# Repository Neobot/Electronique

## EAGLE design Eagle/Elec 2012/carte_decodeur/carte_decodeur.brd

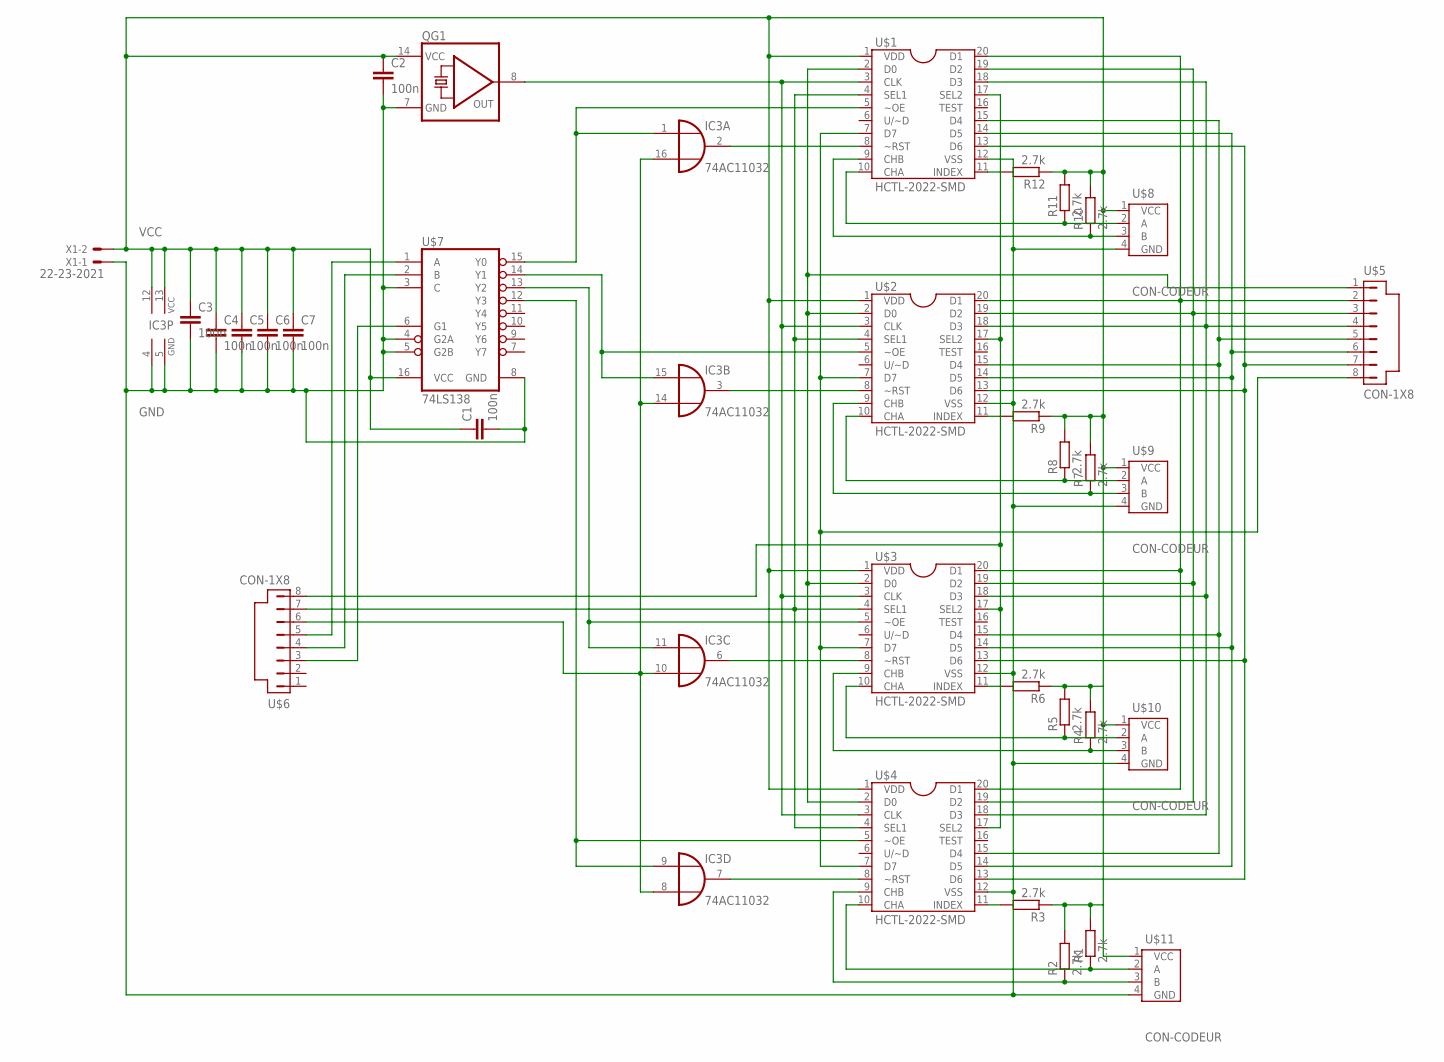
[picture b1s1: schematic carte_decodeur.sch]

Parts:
C1, C2, C3, C4, C5, C6, C7: 100n; C0805
IC3: 74AC11032; DIL16
QG1: QG5860; DIL14S
R1, R2, R3, R4, R5, R6, R7, R8, R9, R10, R11, R12: 2.7k; R0805
U$1, U$2, U$3, U$4: HCTL-2022-SMD; DIL20-SMD
U$5, U$6: CON-1X8
U$7: 74LS138; DIL16
U$8, U$9, U$10, U$11: CON-CODEUR; CON-1X4
X1: 22-23-2021

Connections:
GND: C1.2, C2.2, C3.2, C4.2, C5.2, C6.2, C7.2, IC3.4 (GND), IC3.5 (GND), QG1.7 (GND), U$1.12 (VSS), U$2.12 (VSS), U$3.12 (VSS), U$4.12 (VSS), U$7.3 (C), U$7.4 (G2A), U$7.5 (G2B), U$7.8 (GND), U$8.4 (GND), U$9.4 (GND), U$10.4 (GND), U$11.4 (GND), X1.1
unnamed: U$1.15 (D4), U$2.15 (D4), U$3.15 (D4), U$4.15 (D4), U$5.5
unnamed: U$1.19 (D2), U$2.19 (D2), U$3.19 (D2), U$4.19 (D2), U$5.3
unnamed: U$1.18 (D3), U$2.18 (D3), U$3.18 (D3), U$4.18 (D3), U$5.4
unnamed: IC3.1 (I1), U$1.5 (~OE), U$7.15 (Y0)
unnamed: IC3.15 (I1), U$2.5 (~OE), U$7.14 (Y1)
unnamed: U$1.13 (D6), U$2.13 (D6), U$3.13 (D6), U$4.13 (D6), U$5.7
unnamed: U$1.7 (D7), U$2.7 (D7), U$3.7 (D7), U$4.7 (D7), U$5.8
unnamed: U$1.2 (D0), U$2.2 (D0), U$3.2 (D0), U$4.2 (D0), U$5.1
unnamed: U$1.20 (D1), U$2.20 (D1), U$3.20 (D1), U$4.20 (D1), U$5.2
unnamed: IC3.11 (I1), U$3.5 (~OE), U$7.13 (Y2)
unnamed: IC3.9 (I1), U$4.5 (~OE), U$7.12 (Y3)
unnamed: U$1.4 (SEL1), U$2.4 (SEL1), U$3.4 (SEL1), U$4.4 (SEL1), U$6.7
unnamed: U$1.17 (SEL2), U$2.17 (SEL2), U$3.17 (SEL2), U$4.17 (SEL2), U$6.8
unnamed: U$1.14 (D5), U$2.14 (D5), U$3.14 (D5), U$4.14 (D5), U$5.6
unnamed: U$6.5, U$7.1 (A)
unnamed: U$6.4, U$7.2 (B)
unnamed: IC3.7 (O), U$4.8 (~RST)
unnamed: IC3.6 (O), U$3.8 (~RST)
unnamed: IC3.3 (O), U$2.8 (~RST)
unnamed: IC3.2 (O), U$1.8 (~RST)
unnamed: U$6.3, U$7.6 (G1)
unnamed: IC3.8 (I2), IC3.10 (I2), IC3.14 (I2), U$6.6
unnamed: R1.1, U$4.10 (CHA), U$11.2 (A)
unnamed: R2.1, U$4.9 (CHB), U$11.3 (B)
unnamed: QG1.8 (OUT), U$1.3 (CLK), U$2.3 (CLK), U$3.3 (CLK), U$4.3 (CLK)
unnamed: R3.2, U$4.11 (INDEX)
unnamed: R5.1, U$3.10 (CHA), U$10.2 (A)
unnamed: R4.1, U$3.9 (CHB), U$10.3 (B)
unnamed: R6.2, U$3.11 (INDEX)
unnamed: R9.2, U$2.11 (INDEX)
unnamed: R8.1, U$2.10 (CHA), U$9.2 (A)
unnamed: R7.1, U$2.9 (CHB), U$9.3 (B)
unnamed: R12.2, U$1.11 (INDEX)
unnamed: R11.1, U$1.10 (CHA), U$8.2 (A)
unnamed: R10.1, U$1.9 (CHB), U$8.3 (B)
VCC: C1.1, C2.1, C3.1, C4.1, C5.1, C6.1, C7.1, IC3.12 (VCC), IC3.13 (VCC), QG1.14 (VCC), R1.2, R2.2, R3.1, R4.2, R5.2, R6.1, R7.2, R8.2, R9.1, R10.2, R11.2, R12.1, U$1.1 (VDD), U$2.1 (VDD), U$3.1 (VDD), U$4.1 (VDD), U$7.16 (VCC), U$8.1 (VCC), U$9.1 (VCC), U$10.1 (VCC), U$11.1 (VCC), X1.2

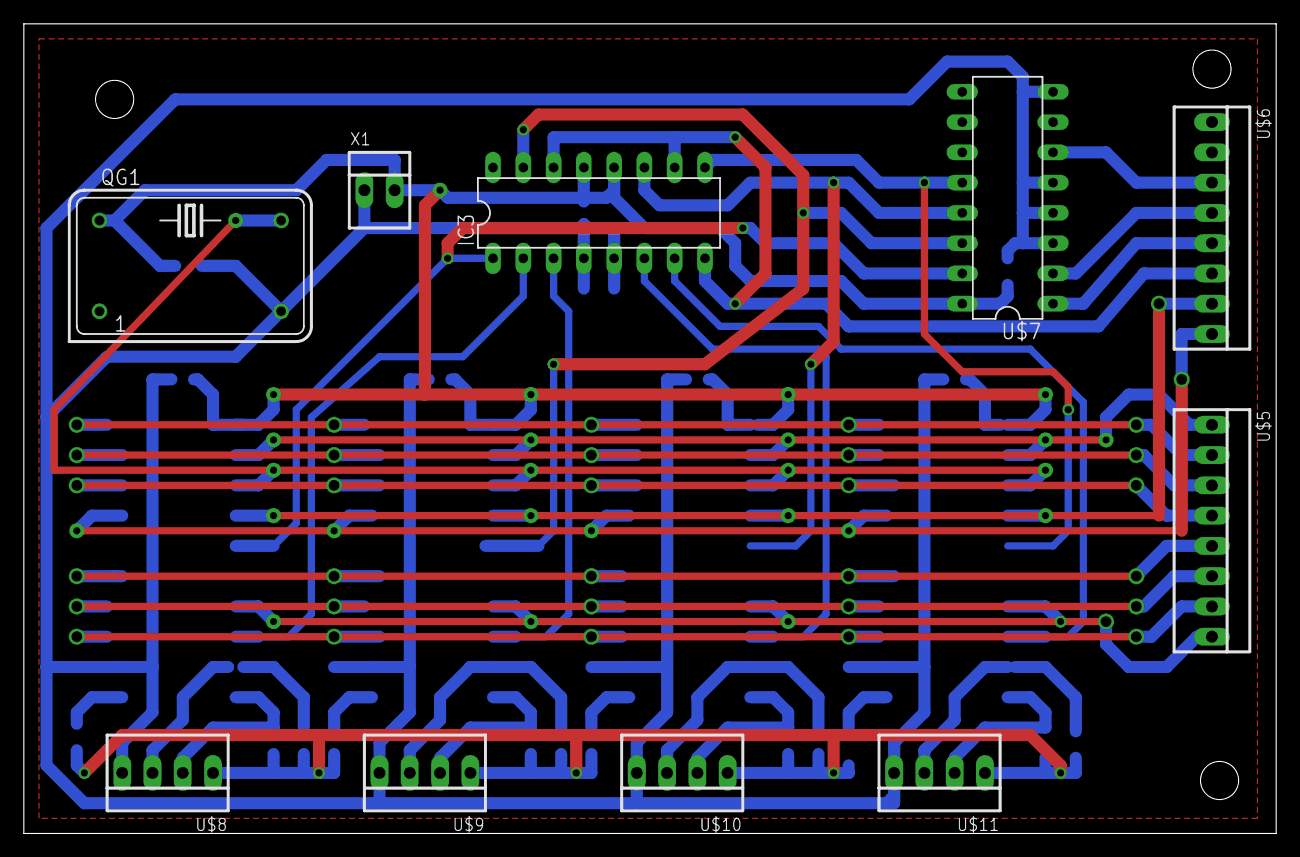
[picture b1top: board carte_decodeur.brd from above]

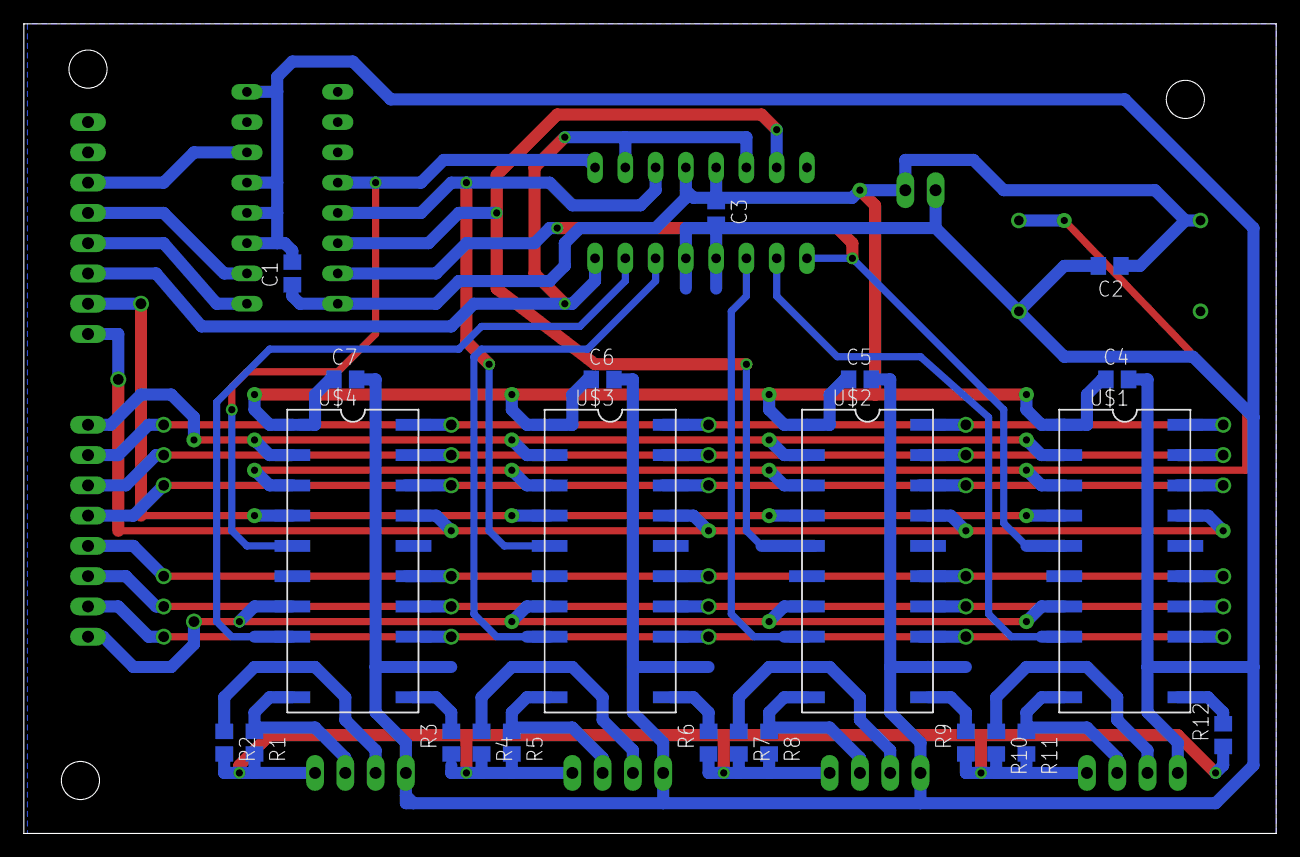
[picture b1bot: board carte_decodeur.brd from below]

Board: 2 copper layers, 105.1 x 67.9 mm, 33 parts (23 on the bottom side), 37 nets.

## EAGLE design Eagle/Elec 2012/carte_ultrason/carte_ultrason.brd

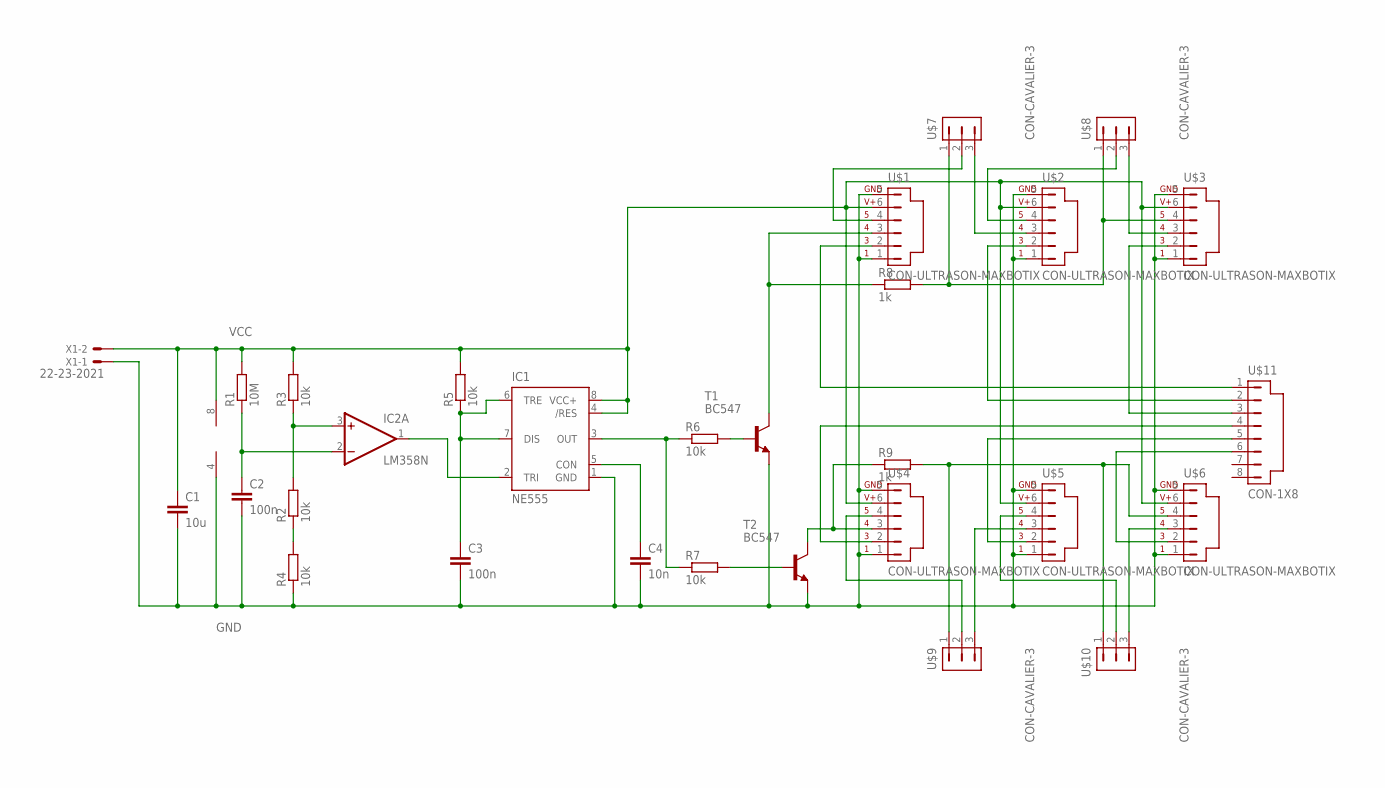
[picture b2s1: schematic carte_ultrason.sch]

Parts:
C1: 10u; C1206K
C2, C3: 100n; C0805K
C4: 10n; C0805K
IC1: NE555; DIL-08
IC2: LM358N; DIL08
R1: 10M; R0805W
R2, R4, R5: 10k; R0805W
R3, R6, R7: 10k; 0207/10
R8: 1k; 0207/10
R9: 1k; R0805W
T1, T2: BC547; TO92
U$1, U$2, U$3, U$4, U$5, U$6: CON-ULTRASON-MAXBOTIX; CON-1X6
U$7, U$8, U$9, U$10: CON-CAVALIER-3
U$11: CON-1X8
X1: 22-23-2021

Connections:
GND: C1.2, C2.2, C3.2, C4.2, IC1.1 (GND), IC2.4 (V-), R4.1, T1.1 (E), T2.1 (E), U$1.1, U$1.5 (GND), U$2.1, U$2.5 (GND), U$3.1, U$3.5 (GND), U$4.1, U$4.5 (GND), U$5.1, U$5.5 (GND), U$6.1, U$6.5 (GND), X1.1
unnamed: IC1.2 (TRI), IC2.1 (OUT)
unnamed: C3.1, IC1.6 (TRE), IC1.7 (DIS), R5.1
unnamed: C2.1, IC2.2 (-IN), R1.1
unnamed: R2.1, R4.2
unnamed: IC2.3 (+IN), R2.2, R3.1
unnamed: C4.1, IC1.5 (CON)
unnamed: IC1.3 (OUT), R6.1, R7.1
unnamed: R6.2, T1.2 (B)
unnamed: R7.2, T2.2 (B)
unnamed: U$1.4, U$7.2
unnamed: R9.1, T2.3 (C), U$4.3
unnamed: U$6.2, U$11.6
unnamed: U$2.3, U$7.3
unnamed: U$2.4, U$8.2
unnamed: U$3.3, U$8.3
unnamed: U$4.4, U$9.2
unnamed: R9.2, U$6.4, U$9.1, U$10.1
unnamed: U$5.3, U$9.3
unnamed: U$5.4, U$10.2
unnamed: U$6.3, U$10.3
unnamed: U$5.2, U$11.5
unnamed: R8.2, U$3.4, U$7.1, U$8.1
unnamed: U$4.2, U$11.4
unnamed: U$1.2, U$11.1
unnamed: U$3.2, U$11.3
unnamed: U$2.2, U$11.2
unnamed: R8.1, T1.3 (C), U$1.3
VCC: C1.1, IC1.4 (/RES), IC1.8 (VCC+), IC2.8 (V+), R1.2, R3.2, R5.2, U$1.6 (V+), U$2.6 (V+), U$3.6 (V+), U$4.6 (V+), U$5.6 (V+), U$6.6 (V+), X1.2

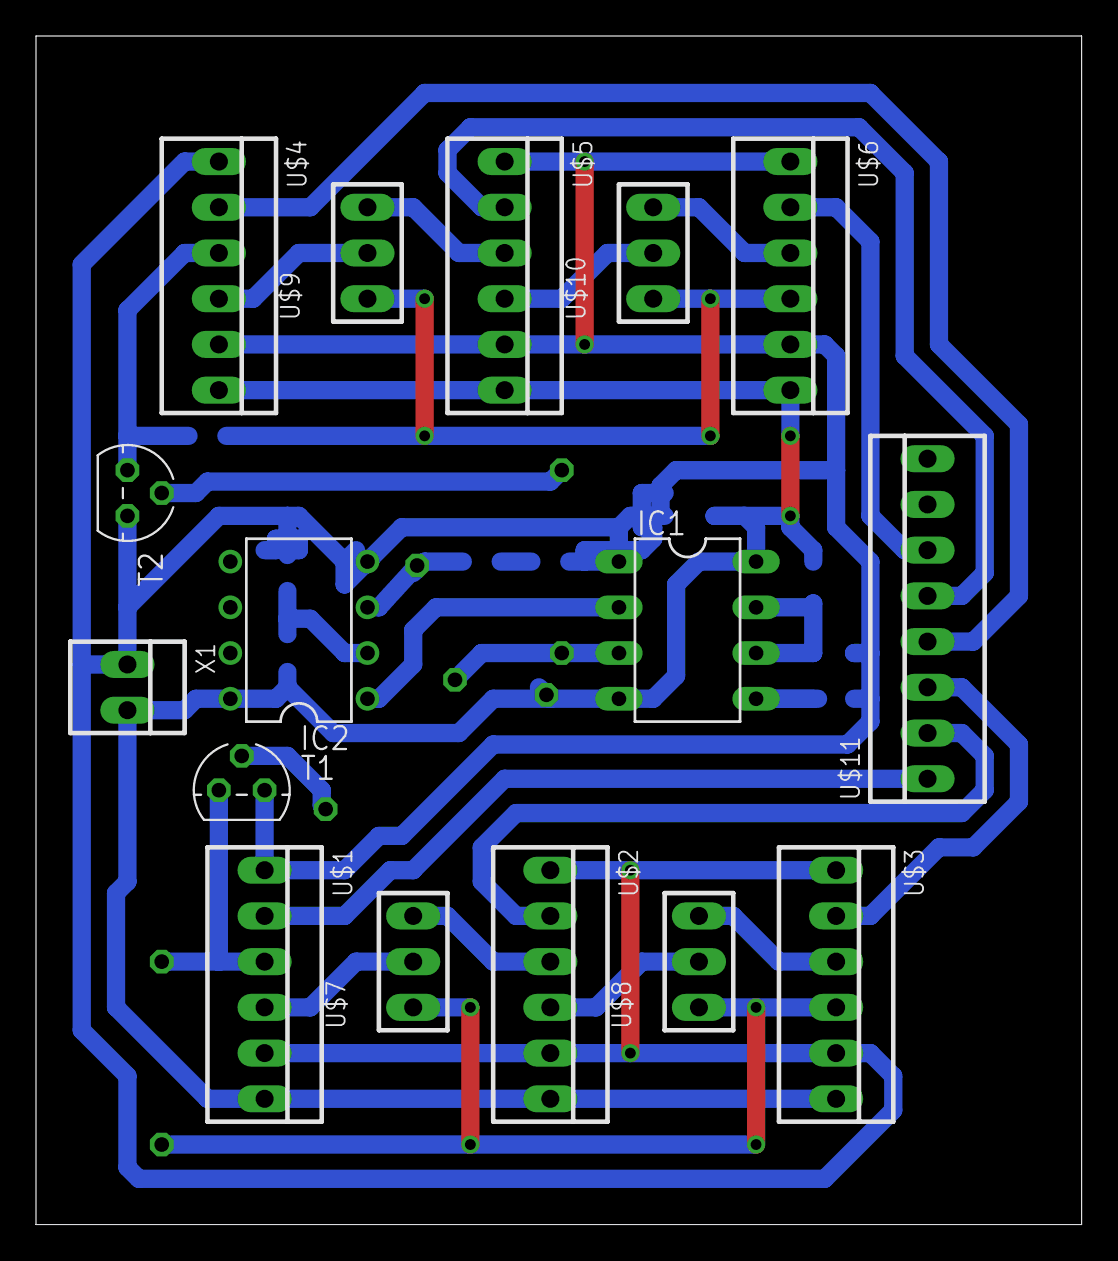
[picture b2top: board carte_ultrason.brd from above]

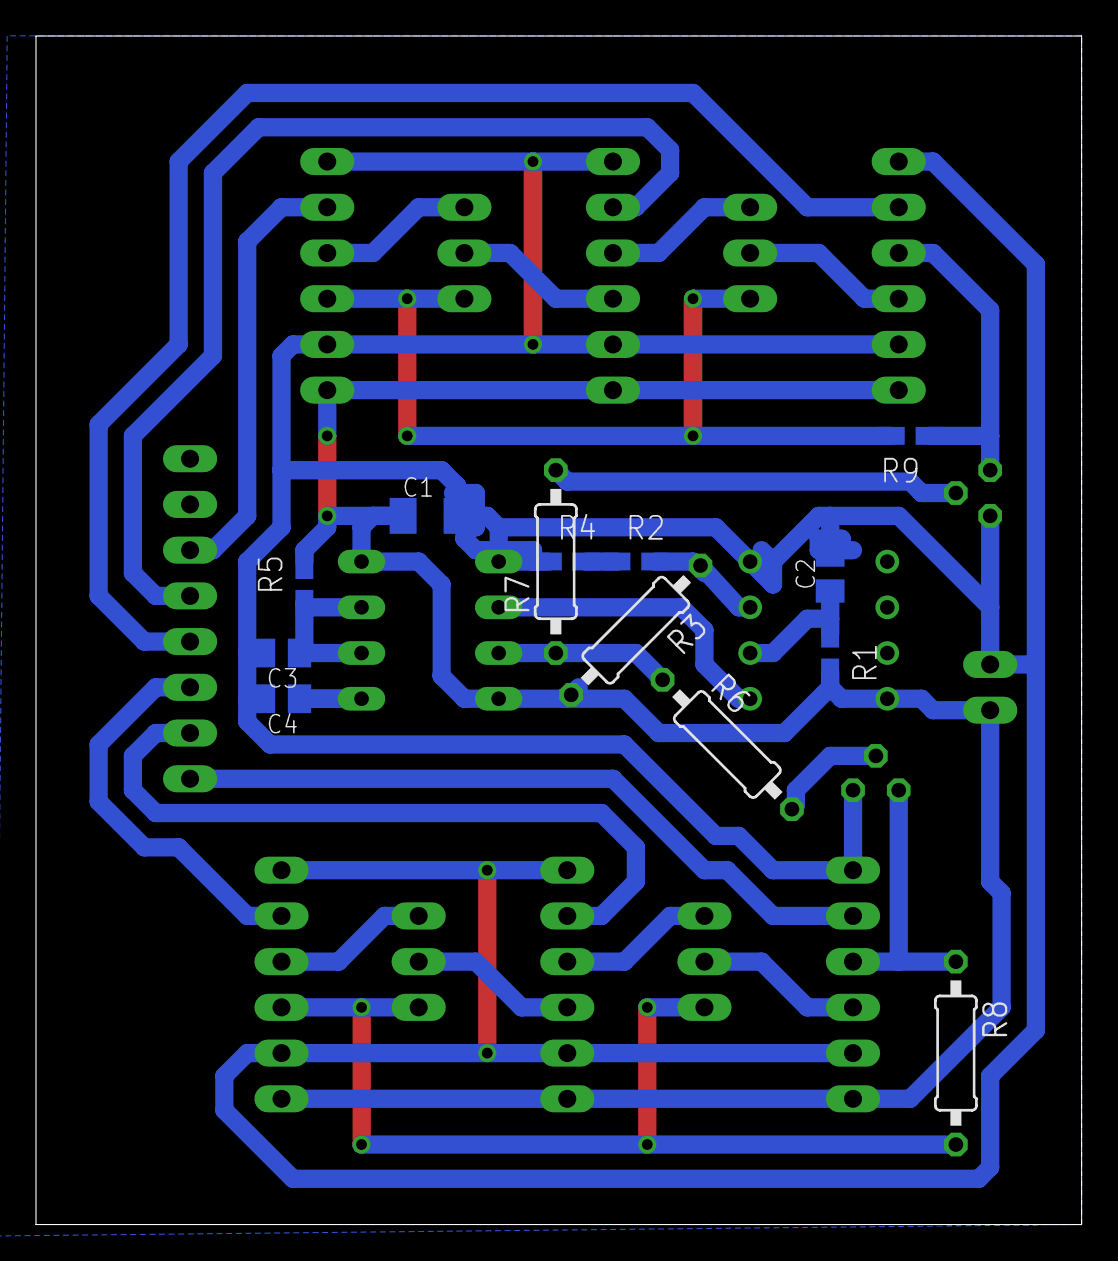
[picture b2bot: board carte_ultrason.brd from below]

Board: 2 copper layers, 58.1 x 66.0 mm, 29 parts (13 on the bottom side), 29 nets.

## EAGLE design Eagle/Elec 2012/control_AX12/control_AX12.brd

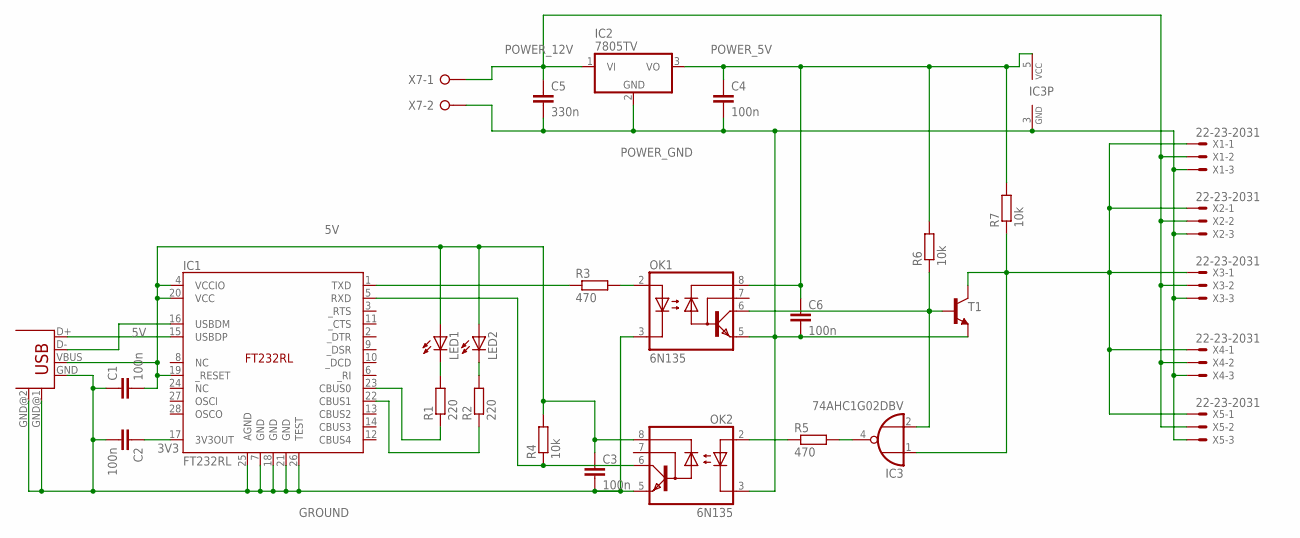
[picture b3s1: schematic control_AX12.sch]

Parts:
C1, C2, C3, C4, C6: 100n; C0805
C5: 330n; C0805
IC1: FT232RL; SSOP-28
IC2: 7805TV; TO220V
IC3: 74AHC1G02DBV; SOT23-5
LED1, LED2: LED5MM
OK1, OK2: 6N135; DIL08
R1, R2: 220; M0805
R3, R5: 470; 0207/10
R4, R6, R7: 10k; 0207/10
T1: BC547-NPN-TO92-CBE; TO92-CBE
USB1: USB-B-H
X1, X2, X3, X4, X5: 22-23-2031
X7: W237-02P; W237-132

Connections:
3V3: C2.1, IC1.17 (3V3OUT)
5V: C1.2, C3.1, IC1.4 (VCCIO), IC1.19 (_RESET), IC1.20 (VCC), LED1.A, LED2.A, OK2.8 (VCC), R4.2, USB1.VBUS
GROUND: C1.1, C2.2, C3.2, IC1.7 (GND), IC1.18 (GND), IC1.21 (GND), IC1.25 (AGND), IC1.26 (TEST), OK1.3 (C), OK2.5 (GND), USB1.GND, USB1.GND@1 (GND), USB1.GND@2 (GND)
unnamed: IC1.22 (CBUS1), R2.1
unnamed: IC1.1 (TXD), R3.1
unnamed: IC1.5 (RXD), OK2.6 (VO), R4.1
unnamed: IC1.23 (CBUS0), R1.1
unnamed: LED1.K (C), R1.2
unnamed: LED2.K (C), R2.2
unnamed: OK1.2 (A), R3.2
unnamed: IC1.16 (USBDM), USB1.D-
unnamed: IC1.15 (USBDP), USB1.D+
unnamed: OK2.2 (A), R5.1
unnamed: IC3.4 (O), R5.2
unnamed: IC3.2 (I1), OK1.6 (VO), R6.1, T1.B
unnamed: IC3.1 (I0), R7.1, T1.C, X1.1, X2.1, X3.1, X4.1, X5.1
POWER_5V: C4.1, C6.1, IC2.3 (VO), IC3.5 (VCC), OK1.8 (VCC), R6.2, R7.2
POWER_12V: C5.1, IC2.1 (VI), X1.2, X2.2, X3.2, X4.2, X5.2, X7.1
POWER_GND: C4.2, C5.2, C6.2, IC2.2 (GND), IC3.3 (GND), OK1.5 (GND), OK2.3 (C), T1.E, X1.3, X2.3, X3.3, X4.3, X5.3, X7.2

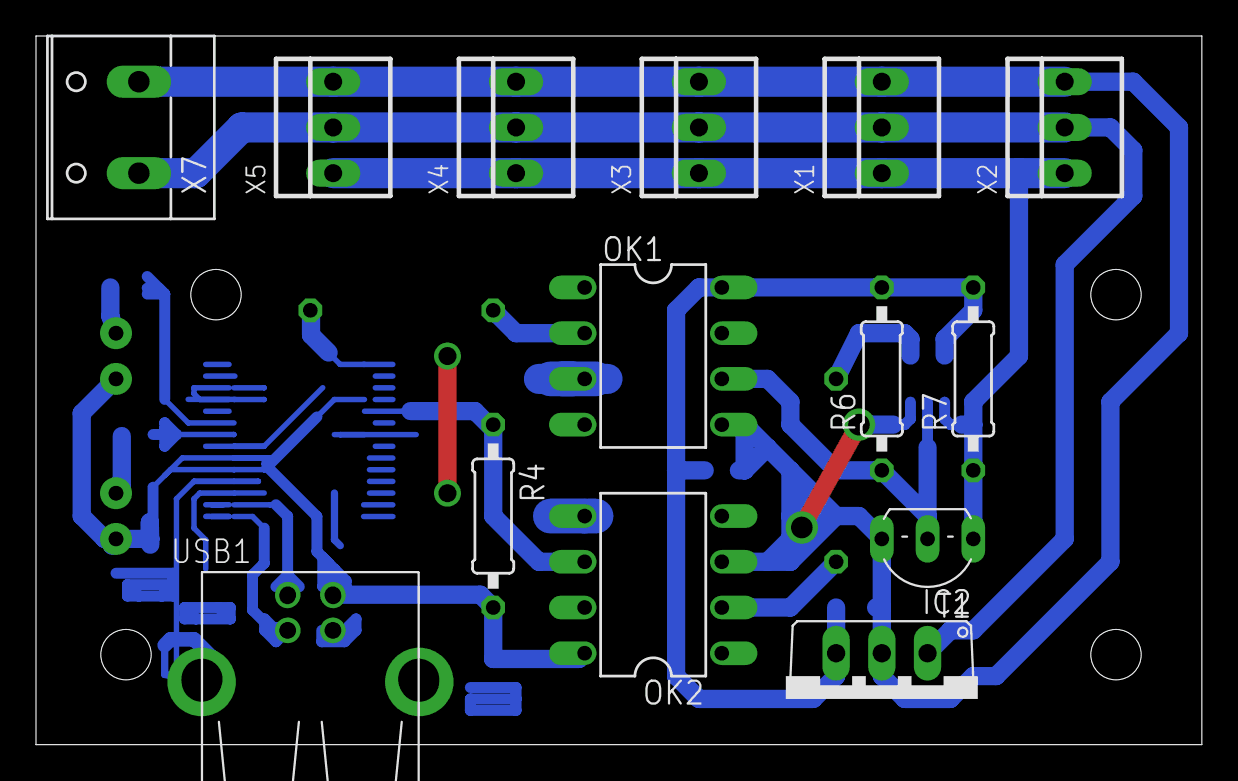
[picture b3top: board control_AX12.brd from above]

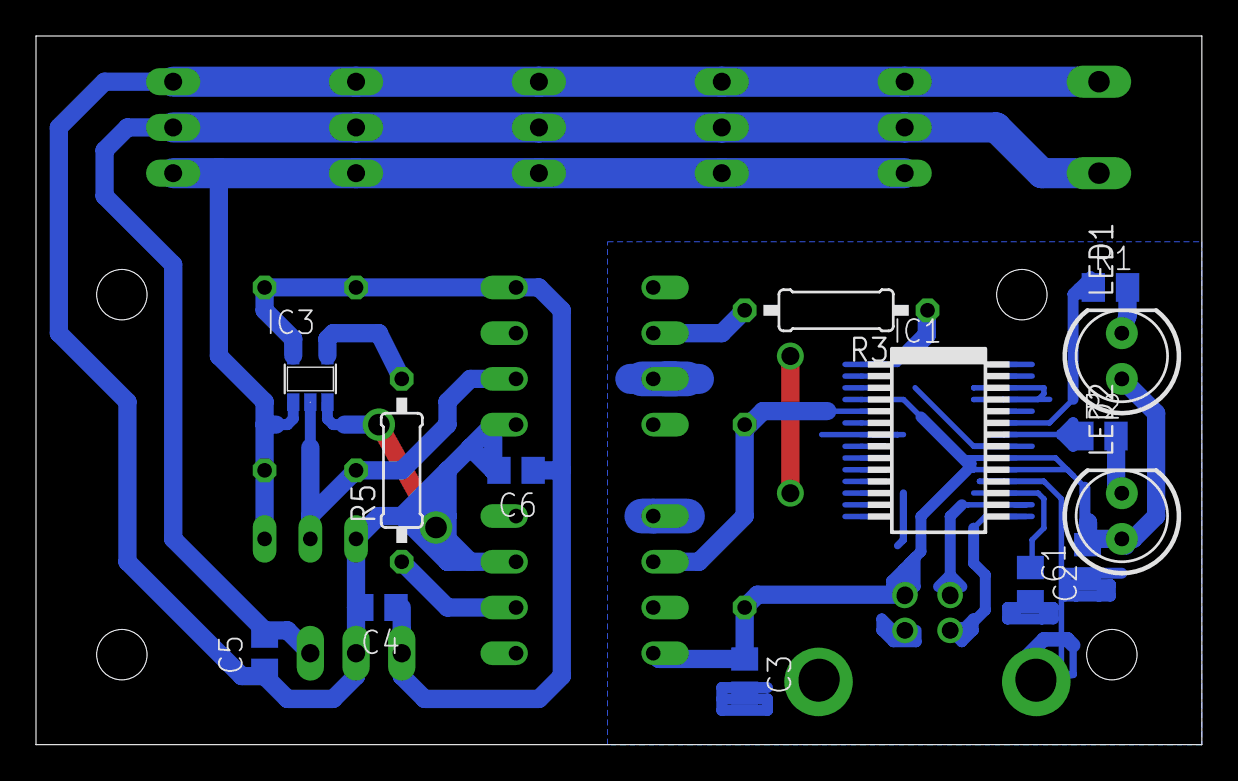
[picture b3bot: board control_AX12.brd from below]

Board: 2 copper layers, 64.8 x 39.4 mm, 28 parts (14 on the bottom side), 19 nets.

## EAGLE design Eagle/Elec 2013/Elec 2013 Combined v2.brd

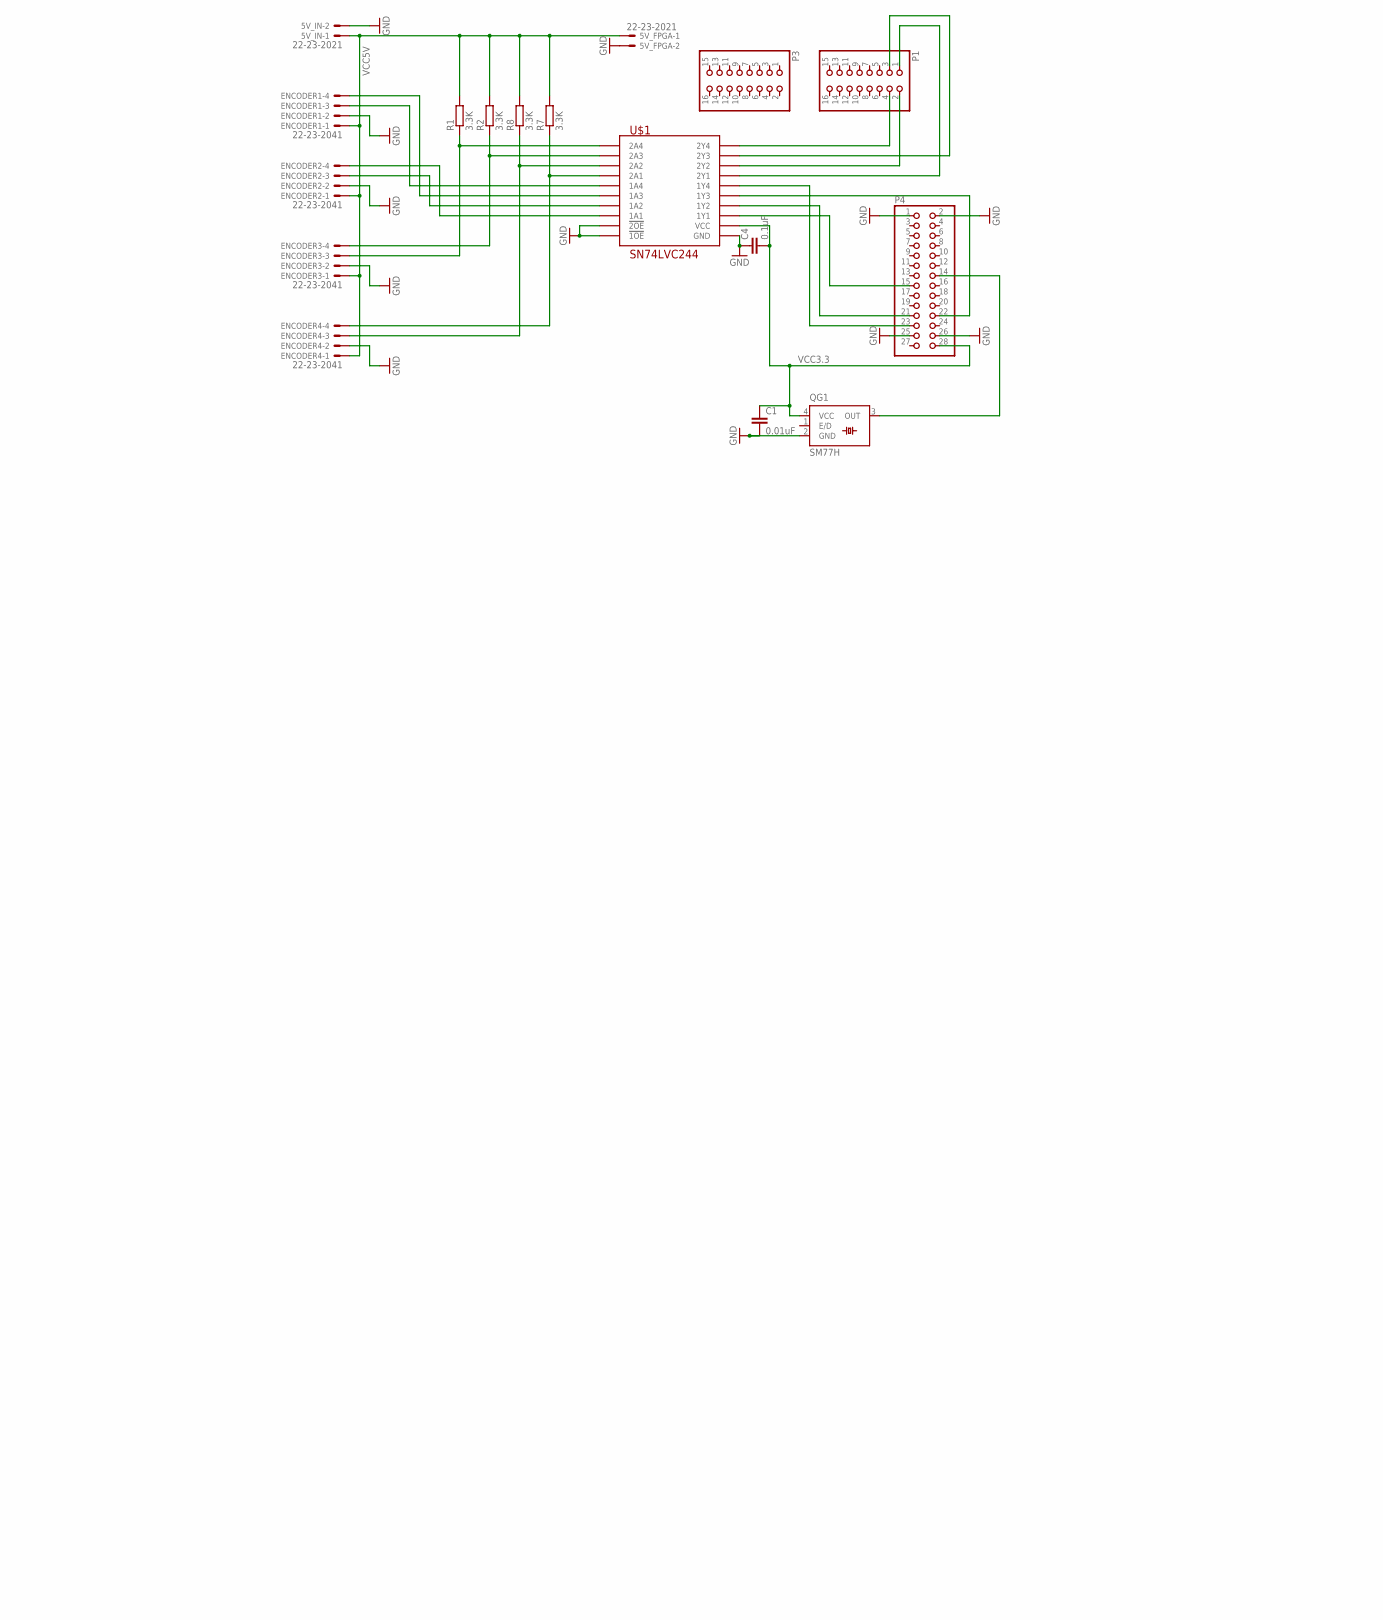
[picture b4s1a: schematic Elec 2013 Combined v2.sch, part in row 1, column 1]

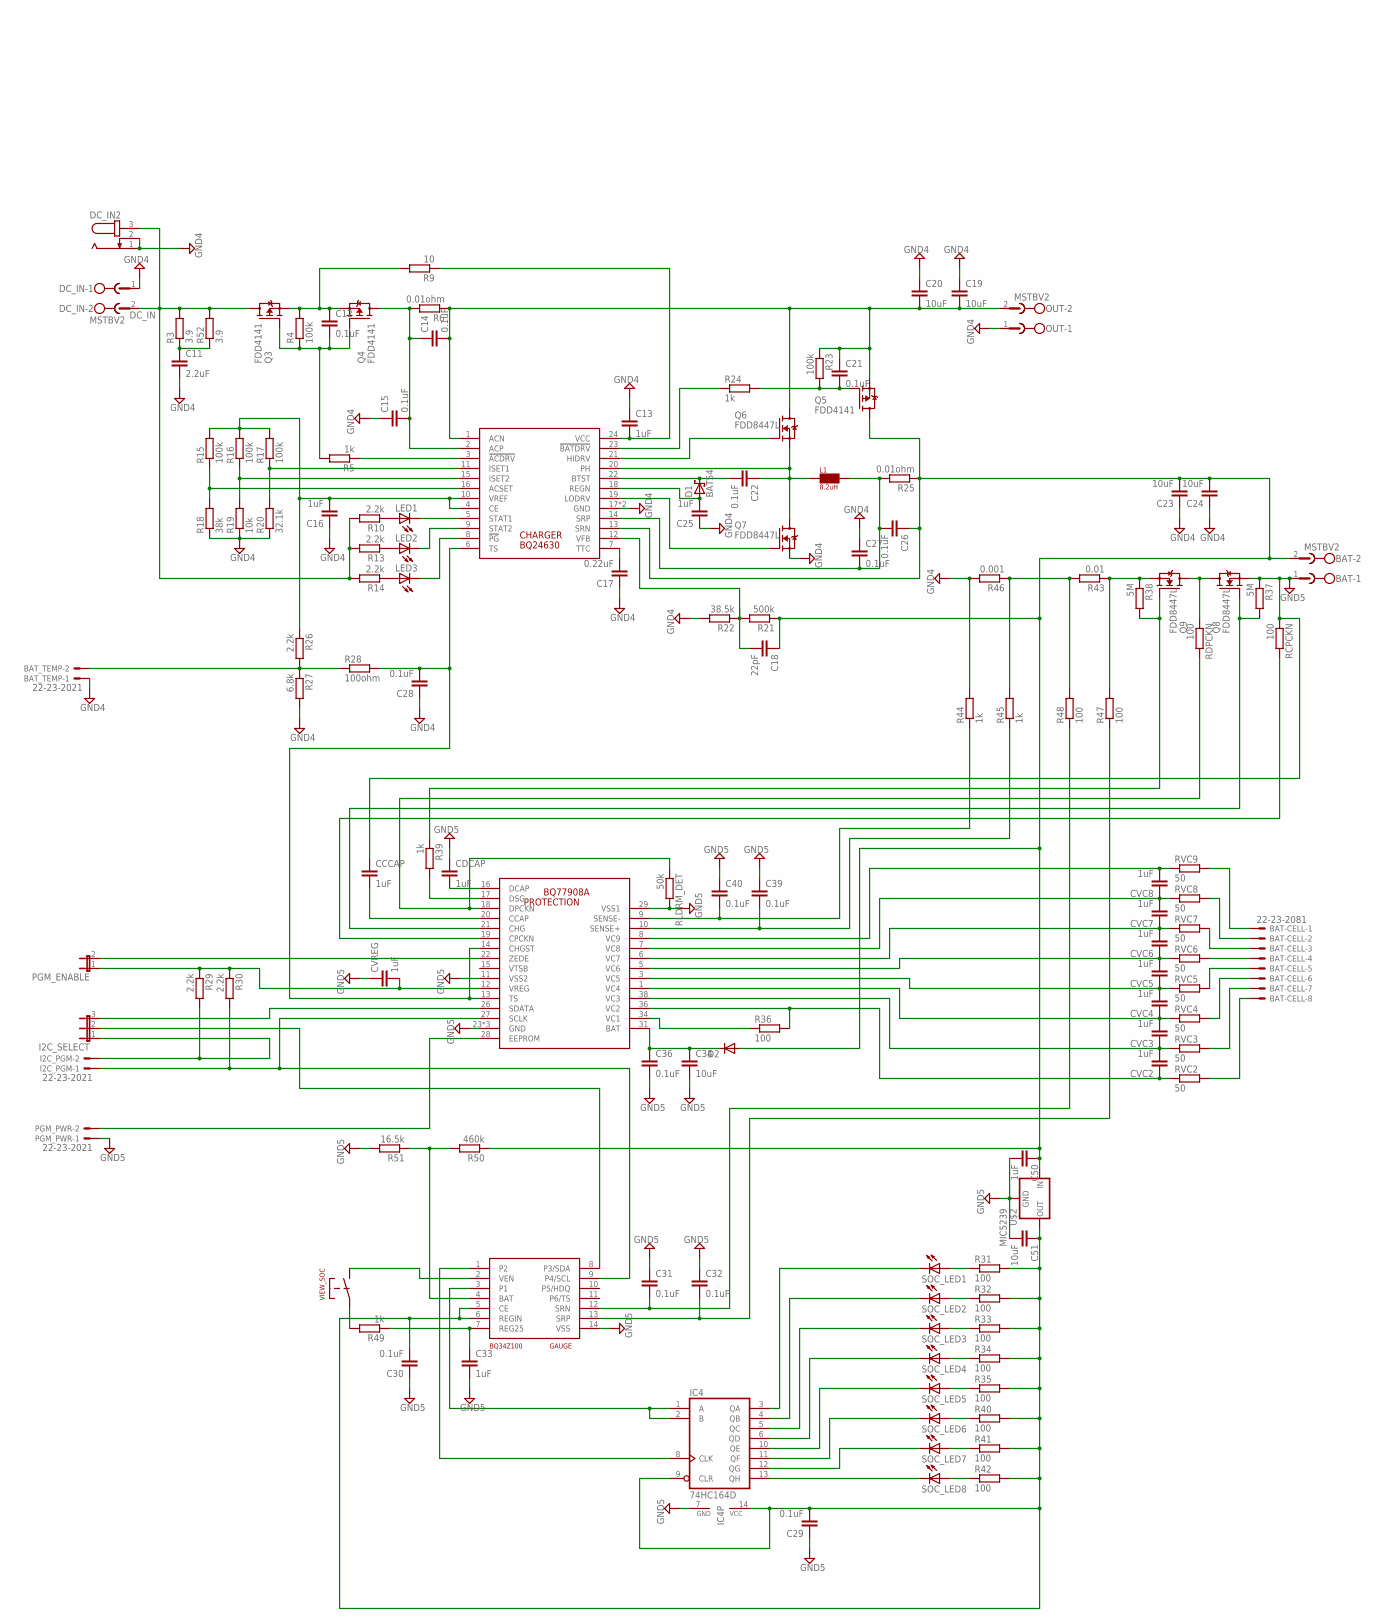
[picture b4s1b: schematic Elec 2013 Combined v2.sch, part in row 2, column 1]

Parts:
5V_FPGA: 22-23-2021; MPN 22-23-2021
5V_IN: 22-23-2021
BAT: MSTBV2; MPN MSTBV 2,5/2-GF-5.08
BAT-CELL: 22-23-2081
BAT_TEMP: 22-23-2021; MPN 22-23-2021
C1: 0.01uF; C0603
C4, C12, C14, C15, C21, C22, C26, C27, C28, C29, C30, C31, C32, C39, C40: 0.1uF; C0603
C11: 2.2uF; C1206
C13: 1uF; C1206
C16, C25: 1uF; C0805
C17: 0.22uF; C0603
C18: 22pF; C0603
C19, C20, C23, C24: 10uF; C1812
C33, C50: 1uF; C0603
C34: 10uF; C1210
C36: 0.1uF; C1210
C51: 10uF; C0603
CCCAP: 1uF; C1206
CDCAP: 1uF; C1206
CHARGER: BQ24630; QFN-24
CVC2, CVC3, CVC4, CVC5, CVC6, CVC7, CVC8: 1uF; C0603
CVREG: 1uF; C0603
D1: BAT54; SOT23
D2: DIODE-SOD123; SOD123
DC_IN: MSTBV2
DC_IN2: JACK-PLUG1; SPC4078
ENCODER1, ENCODER2, ENCODER3, ENCODER4: 22-23-2041
GAUGE: BQ34Z100; TSSOP-14-0.65MM
I2C_PGM: 22-23-2021; MPN 22-23-2021
I2C_SELECT: JP2E; JP2
IC4: 74HC164D; SO14
L1: 8.2uH; 5050CE
LED1, LED2, LED3: LEDCHIP-LED0603; CHIP-LED0603
OUT: MSTBV2; MPN MSTBV 2,5/2-GF-5.08
P1, P3: PINHD-2X8; 2X08
P4: PINHD-2X14; 2X14
PGM_ENABLE: JP1E; JP1
PGM_PWR: 22-23-2021; MPN 22-23-2021
PROTECTION: BQ77908A; TSSOP-38-0.5MM
Q3, Q4, Q5: FDD4141; TO252
Q6, Q7, Q8, Q9: FDD8447L; TO252
QG1: SM77H
R1, R2, R7, R8: 3.3K; R0603
R3, R52: 3.9; R1206
R4, R23: 100k; R0603
R5, R24, R39, R44, R45, R49: 1k; R0603
R6, R25: 0.01ohm; R2010
R9: 10; R1206
R10, R13, R14, R26, R29, R30: 2.2k; R0603
R15, R16, R17: 100k; R0805
R18: 38k; R0805
R19: 10k; R0805
R20: 32.1k; R0805
R21: 500k; R0805
R22: 38.5k; R0805
R27: 6.8k; R0603
R28: 100ohm; R0603
R31, R32, R33, R34, R35, R36, R40, R41, R42, R47, R48: 100; R0603
R37, R38: 5M; R0603
R43: 0.01; R2010
R46: 0.001; R2010
R50: 460k; R0805
R51: 16.5k; R0603
RCPCKN: 100; R0603
RDPCKN: 100; R0603
RLDRM_DET: 50k; R0603
RVC2, RVC3, RVC4, RVC5, RVC6, RVC7, RVC8, RVC9: 50; R1206
SOC_LED1, SOC_LED2, SOC_LED3, SOC_LED4, SOC_LED5, SOC_LED6, SOC_LED7, SOC_LED8: LEDCHIP-LED0603; CHIP-LED0603
U$1: SN74LVC244; TSSOP-20-0.65MM
U$2: MIC5239; SOT223
VIEW_SOC: PUSHBUTTON

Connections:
DC_IN: DC_IN.2, DC_IN2.3, Q3.3 (D), R3.2, R10.2, R13.2, R14.2, R52.2
GND: 5V_FPGA.2, 5V_IN.2, C1.2, C4.1, ENCODER1.2, ENCODER2.2, ENCODER3.2, ENCODER4.2, P4.1, P4.2, P4.25, P4.26, QG1.2 (GND), U$1.P$1 (!1OE), U$1.P$10 (GND), U$1.P$19 (!2OE)
GND4: BAT_TEMP.1, C11.2, C13.1, C15.1, C16.1, C17.1, C19.1, C20.1, C23.1, C24.1, C25.1, C27.1, C28.1, CHARGER.17 (GND), CHARGER.THERMAL (GND), DC_IN.1, DC_IN2.1, DC_IN2.2, OUT.1, Q7.2 (S), R18.1, R19.1, R20.1, R22.2, R27.2, R44.2, R46.2
GND5: BAT.1, C29.1, C30.1, C31.1, C32.1, C33.2, C34.2, C36.2, C39.1, C40.1, C50.2, C51.2, CCCAP.1, CDCAP.1, CVREG.1, GAUGE.14 (VSS), IC4.7 (GND), PGM_PWR.1, PROTECTION.11 (VSS2), PROTECTION.23 (GND), PROTECTION.24 (GND), PROTECTION.25 (GND), PROTECTION.29 (VSS1), Q8.2 (S), R37.1, R51.2, RCPCKN.1, RLDRM_DET.2, U$2.2 (GND), U$2.4 (GND)
unnamed: P4.14, QG1.3 (OUT)
unnamed: P4.23, U$1.P$12 (1Y4)
unnamed: P4.21, U$1.P$16 (1Y2)
unnamed: P4.15, U$1.P$18 (1Y1)
unnamed: P4.22, U$1.P$14 (1Y3)
unnamed: P1.4, U$1.P$3 (2Y4)
unnamed: P1.2, U$1.P$7 (2Y2)
unnamed: P1.1, U$1.P$9 (2Y1)
unnamed: P1.3, U$1.P$5 (2Y3)
unnamed: ENCODER3.3, R1.1, U$1.P$17 (2A4)
unnamed: ENCODER3.4, R2.1, U$1.P$15 (2A3)
unnamed: C11.1, R3.1, R52.1
unnamed: ENCODER4.3, R8.1, U$1.P$13 (2A2)
unnamed: ENCODER4.4, R7.1, U$1.P$11 (2A1)
unnamed: ENCODER1.3, U$1.P$8 (1A4)
unnamed: ENCODER1.4, U$1.P$6 (1A3)
unnamed: ENCODER2.3, U$1.P$4 (1A2)
unnamed: ENCODER2.4, U$1.P$2 (1A1)
unnamed: C12.1, Q3.2 (S), Q4.2 (S), R4.2, R9.2
unnamed: C12.2, Q3.1 (G), Q4.1 (G), R4.1, R5.2
unnamed: CHARGER.3 (!ACDRV!), R5.1
unnamed: C17.2, CHARGER.7 (TTC)
unnamed: C13.2, CHARGER.24 (VCC), R9.1
unnamed: C14.2, C19.2, C20.2, C21.1, CHARGER.1 (ACN), OUT.2, Q5.2 (S), Q6.3 (D), R6.1, R23.1
unnamed: C18.2, CHARGER.12 (VFB), R21.2, R22.1
unnamed: CHARGER.5 (STAT1), LED1.C
unnamed: CHARGER.9 (STAT2), LED2.C
unnamed: CHARGER.8 (!PG!), LED3.C
unnamed: LED1.A, R10.1
unnamed: LED2.A, R13.1
unnamed: LED3.A, R14.1
unnamed: BAT_TEMP.2, R26.2, R27.1, R28.1
unnamed: CHARGER.16 (ACSET), R15.1, R18.2
unnamed: CHARGER.15 (ISET2), R16.1, R19.2
unnamed: CHARGER.11 (ISET1), R17.1, R20.2
unnamed: Q8.3 (D), Q9.3 (D), RDPCKN.1
unnamed: C28.2, CHARGER.6 (TS), PROTECTION.13 (TS), PROTECTION.14 (CHGST), R28.2
unnamed: C21.2, Q5.1 (G), R23.2, R24.2
unnamed: C32.2, GAUGE.13 (SRP), R47.1
unnamed: CHARGER.23 (!BATDRV!), R24.1
unnamed: CHARGER.21 (HIDRV), Q6.1 (G)
unnamed: C22.1, CHARGER.20 (PH), L1.P$1, Q6.2 (S), Q7.3 (D)
unnamed: C22.2, CHARGER.22 (BTST), D1.3 (C)
unnamed: C34.1, C36.1, D2.C, PROTECTION.31 (BAT)
unnamed: C26.2, C27.2, CHARGER.14 (SRP), L1.P$2, R25.2
unnamed: BAT-CELL.8, RVC2.2
unnamed: C25.2, CHARGER.18 (REGN), D1.1 (A)
unnamed: CHARGER.19 (LODRV), Q7.1 (G)
unnamed: CVC8.2, PROTECTION.8 (VC9), RVC9.1
unnamed: CVC2.1, PROTECTION.36 (VC2), R36.2, RVC2.1
unnamed: CVC4.2, CVC5.1, PROTECTION.3 (VC5), RVC5.1
unnamed: CVC2.2, CVC3.1, PROTECTION.38 (VC3), RVC3.1
unnamed: PROTECTION.34 (VC1), R36.1
unnamed: CVC6.2, CVC7.1, PROTECTION.6 (VC7), RVC7.1
unnamed: CVC5.2, CVC6.1, PROTECTION.5 (VC6), RVC6.1
unnamed: CVC3.2, CVC4.1, PROTECTION.1 (VC4), RVC4.1
unnamed: BAT-CELL.7, RVC3.2
unnamed: BAT-CELL.6, RVC4.2
unnamed: BAT-CELL.5, RVC5.2
unnamed: BAT-CELL.4, RVC6.2
unnamed: BAT-CELL.3, RVC7.2
unnamed: BAT-CELL.2, RVC8.2
unnamed: BAT-CELL.1, RVC9.2
unnamed: C33.1, GAUGE.7 (REG25), R49.1
unnamed: Q9.1 (G), R38.2, R39.1
unnamed: PROTECTION.21 (CHG), Q8.1 (G), R37.2
unnamed: PROTECTION.17 (DSG), R39.2
unnamed: CDCAP.2, PROTECTION.16 (DCAP)
unnamed: CVC7.2, CVC8.1, PROTECTION.7 (VC8), RVC8.1
unnamed: PROTECTION.18 (DPCKN), RDPCKN.2, RLDRM_DET.1
unnamed: R31.1, SOC_LED1.A
unnamed: PROTECTION.19 (CPCKN), RCPCKN.2
unnamed: CCCAP.2, PROTECTION.20 (CCAP)
unnamed: R32.1, SOC_LED2.A
unnamed: C39.2, PROTECTION.10 (SENSE+), R45.1
unnamed: C40.2, PROTECTION.9 (SENSE-), R44.1
unnamed: GAUGE.9 (P4/SCL), I2C_PGM.1, PROTECTION.27 (SCLK), R30.2
unnamed: I2C_PGM.2, I2C_SELECT.1, R29.2
unnamed: R33.1, SOC_LED3.A
unnamed: PGM_ENABLE.2, PROTECTION.22 (ZEDE)
unnamed: PGM_PWR.2, PROTECTION.28 (EEPROM)
unnamed: C29.2, C30.2, C51.1, GAUGE.5 (CE), GAUGE.6 (REGIN), IC4.9 (CLR), IC4.14 (VCC), R31.2, R32.2, R33.2, R34.2, R35.2, R40.2, R41.2, R42.2, U$2.3 (OUT)
unnamed: R34.1, SOC_LED4.A
unnamed: R35.1, SOC_LED5.A
unnamed: R40.1, SOC_LED6.A
unnamed: R41.1, SOC_LED7.A
unnamed: R42.1, SOC_LED8.A
unnamed: IC4.13 (QH), SOC_LED8.C
unnamed: IC4.3 (QA), SOC_LED1.C
unnamed: IC4.4 (QB), SOC_LED2.C
unnamed: IC4.5 (QC), SOC_LED3.C
unnamed: IC4.6 (QD), SOC_LED4.C
unnamed: IC4.10 (QE), SOC_LED5.C
unnamed: IC4.12 (QG), SOC_LED7.C
unnamed: I2C_SELECT.3, PROTECTION.26 (SDATA)
unnamed: GAUGE.8 (P3/SDA), I2C_SELECT.2
unnamed: C31.2, GAUGE.12 (SRN), R48.1
unnamed: GAUGE.3 (P1), IC4.1 (A), IC4.2 (B)
unnamed: GAUGE.1 (P2), IC4.8 (CLK)
unnamed: R49.2, VIEW_SOC.P$1, VIEW_SOC.P$2
unnamed: GAUGE.2 (VEN), VIEW_SOC.P$3, VIEW_SOC.P$4
unnamed: GAUGE.4 (BAT), R50.2, R51.1
unnamed: BAT.2, C18.1, C23.2, C24.2, C26.1, C50.1, CHARGER.13 (SRN), D2.A, Q5.3 (D), R21.1, R25.1, R50.1, U$2.1 (IN)
unnamed: CVREG.2, PGM_ENABLE.1, PROTECTION.12 (VREG), R29.1, R30.1
unnamed: R43.2, R45.2, R46.1, R48.2
unnamed: Q9.2 (S), R38.1, R43.1, R47.2
SI7617DN: C14.1, C15.2, CHARGER.2 (ACP), Q4.3 (D), R6.2
SOC_LED6: IC4.11 (QF), SOC_LED6.C
VCC3.3: C1.1, C4.2, P4.28, QG1.4 (VCC), U$1.P$20 (VCC)
VCC5V: 5V_FPGA.1, 5V_IN.1, ENCODER1.1, ENCODER2.1, ENCODER3.1, ENCODER4.1, R1.2, R2.2, R7.2, R8.2
VREF: C16.2, CHARGER.4 (CE), CHARGER.10 (VREF), R15.2, R16.2, R17.2, R26.1
